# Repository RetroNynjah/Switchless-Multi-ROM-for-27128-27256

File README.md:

# Switchless Multi-ROM for 27128 & 27256 ROMs

<br/>

A switchless multi-ROM for 27128 and 27256 ROM (28-pin) type applications. The switch is controlled by an MCU that is picking up predefined magic words on the data bus.  
This is a more generic and further developed version of my previous 1541-II Multi-ROM design.

Example use cases:
* ROM switch for Commodore disk drives controlled by DOS commands.
* Menu driven Kernal switch for Commodore C64 (shortboards), Commodore C128 and Commodore TED series.
* You tell me

Check the Applications folder for examples on how to use it for the use cases above.

Check the Technical Guide for a general technical description, build instructions and BOM.

  <br/>

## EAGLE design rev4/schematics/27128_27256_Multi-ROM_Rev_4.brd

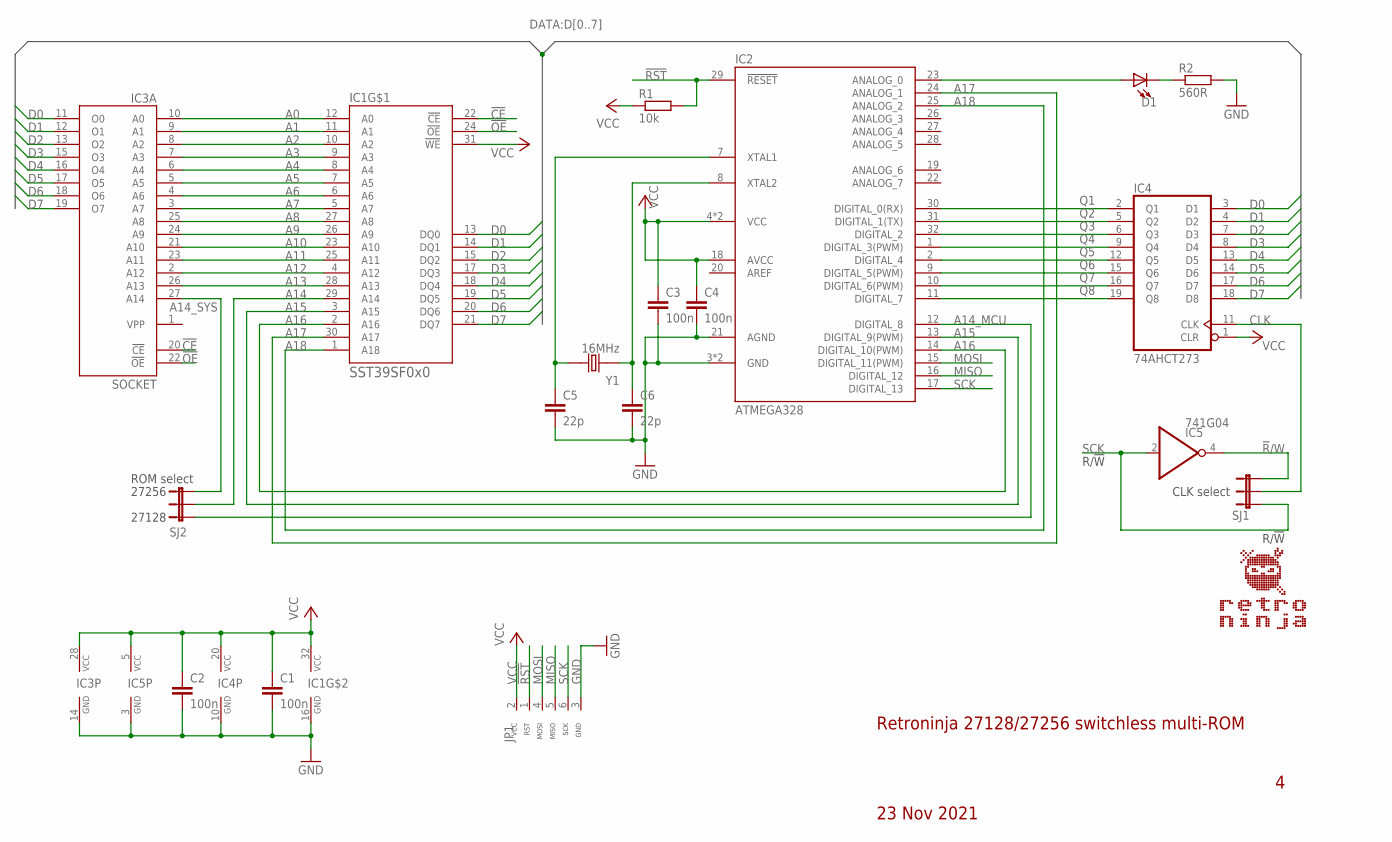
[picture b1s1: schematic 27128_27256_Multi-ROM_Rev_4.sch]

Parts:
C1, C2, C3, C4: 100n; C0805
C5, C6: 22p; C0805
D1: LED_0805; LED0805
IC1: SST39SF0x0; PLCC32_SHORT
IC2: ATMEGA328; TQFP32
IC3: SOCKET; DIL28-6_DOWNPINS
IC4: 74AHCT273; SO20
IC5: 741G04; SOT23-5
JP1: ICSP_CONNECTOR_TL866_RIGHT2; HEADER_1X6_RIGHT
R1: 10k; R0805
R2: 560R; R0805
SJ1, SJ2: JUMPER-3SJ; SJ-3
Y1: 16MHz; CRYSTAL_SMD-2_7X4X2.3

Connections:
!CE: IC1.22 (!CE), IC3.20 (!CE)
!OE: IC1.24 (!OE), IC3.22 (!OE)
!R!/W: IC5.4 (O), SJ1.3
!RST: IC2.29 (!RESET), JP1.1 (RST), R1.2
A0: IC1.12 (A0), IC3.10 (A0)
A1: IC1.11 (A1), IC3.9 (A1)
A2: IC1.10 (A2), IC3.8 (A2)
A3: IC1.9 (A3), IC3.7 (A3)
A4: IC1.8 (A4), IC3.6 (A4)
A5: IC1.7 (A5), IC3.5 (A5)
A6: IC1.6 (A6), IC3.4 (A6)
A7: IC1.5 (A7), IC3.3 (A7)
A8: IC1.27 (A8), IC3.25 (A8)
A9: IC1.26 (A9), IC3.24 (A9)
A10: IC1.23 (A10), IC3.21 (A10)
A11: IC1.25 (A11), IC3.23 (A11)
A12: IC1.4 (A12), IC3.2 (A12)
A13: IC1.28 (A13), IC3.26 (A13)
A14: IC1.29 (A14), SJ2.2
A14_MCU: IC2.12 (DIGITAL_8), SJ2.1
A14_SYS: IC3.27 (A14), SJ2.3
A15: IC1.3 (A15), IC2.13 (DIGITAL_9(PWM))
A16: IC1.2 (A16), IC2.14 (DIGITAL_10(PWM))
A17: IC1.30 (A17), IC2.24 (ANALOG_1)
A18: IC1.1 (A18), IC2.25 (ANALOG_2)
CLK: IC4.11 (CLK), SJ1.2
D0: IC1.13 (DQ0), IC3.11 (O0), IC4.3 (D1)
D1: IC1.14 (DQ1), IC3.12 (O1), IC4.4 (D2)
D2: IC1.15 (DQ2), IC3.13 (O2), IC4.7 (D3)
D3: IC1.17 (DQ3), IC3.15 (O3), IC4.8 (D4)
D4: IC1.18 (DQ4), IC3.16 (O4), IC4.13 (D5)
D5: IC1.19 (DQ5), IC3.17 (O5), IC4.14 (D6)
D6: IC1.20 (DQ6), IC3.18 (O6), IC4.17 (D7)
D7: IC1.21 (DQ7), IC3.19 (O7), IC4.18 (D8)
GND: C1.2, C2.2, C3.2, C4.2, C5.2, C6.2, IC1.16 (GND), IC2.3 (GND), IC2.5 (GND), IC2.21 (AGND), IC3.14 (GND), IC4.10 (GND), IC5.3 (GND), JP1.3 (GND), R2.2
MISO: IC2.16 (DIGITAL_12), JP1.5 (MISO)
MOSI: IC2.15 (DIGITAL_11(PWM)), JP1.4 (MOSI)
unnamed: C6.1, IC2.8 (XTAL2), Y1.1
unnamed: C5.1, IC2.7 (XTAL1), Y1.2
unnamed: D1.A, IC2.23 (ANALOG_0)
unnamed: D1.C, R2.1
Q1: IC2.30 (DIGITAL_0(RX)), IC4.2 (Q1)
Q2: IC2.31 (DIGITAL_1(TX)), IC4.5 (Q2)
Q3: IC2.32 (DIGITAL_2), IC4.6 (Q3)
Q4: IC2.1 (DIGITAL_3(PWM)), IC4.9 (Q4)
Q5: IC2.2 (DIGITAL_4), IC4.12 (Q5)
Q6: IC2.9 (DIGITAL_5(PWM)), IC4.15 (Q6)
Q7: IC2.10 (DIGITAL_6(PWM)), IC4.16 (Q7)
Q8: IC2.11 (DIGITAL_7), IC4.19 (Q8)
SCK: IC2.17 (DIGITAL_13), IC5.2 (I), JP1.6 (SCK), SJ1.1
VCC: C1.1, C2.1, C3.1, C4.1, IC1.31 (!WE), IC1.32 (VCC), IC2.4 (VCC), IC2.6 (VCC), IC2.18 (AVCC), IC3.28 (VCC), IC4.1 (CLR), IC4.20 (VCC), IC5.5 (VCC), JP1.2 (VCC), R1.1
VPP: IC3.1 (VPP)

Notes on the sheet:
Retroninja 27128/27256 switchless multi-ROM
23 Nov 2021
27128
27256
R/!W
CLK select
ROM select

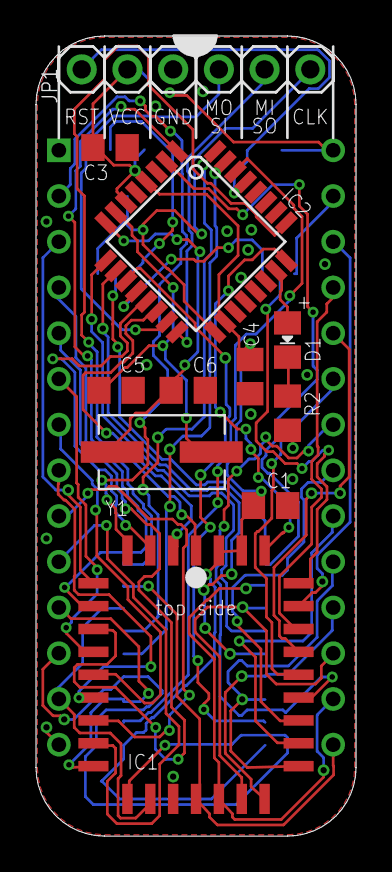
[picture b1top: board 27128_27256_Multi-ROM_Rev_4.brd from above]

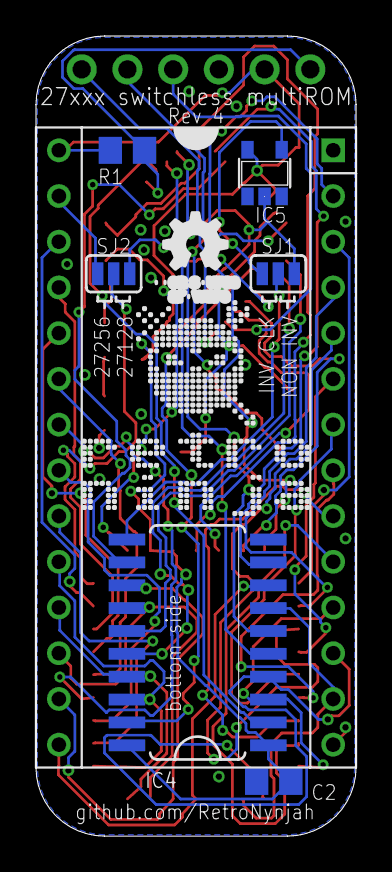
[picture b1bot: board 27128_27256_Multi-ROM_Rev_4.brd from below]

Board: 2 copper layers, 17.8 x 44.5 mm, 20 parts (8 on the bottom side), 51 nets.

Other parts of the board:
U$1: RETRONINJA_12MM
U$2: OSHW_5MM

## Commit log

2022-06-27 Initial upload
2022-08-20 Updated technical guide and multi-kernal user's guide
    Corrected errors in documentation
2022-09-06 Kernal switch C128DCR support
    New mini-kernals that send different commands for C128DCR switches. C64/C128 mini-kernal version numbers aligned.
    Added C128DCR firmware v 1.2. version number aligned with C128 firmware.
    Updated Kernal switch user guide to version 1.2 with added C128DCR solder point locations.
2022-09-06 Updated Kernal switch pictures and corrected user guide version
2022-09-07 Updated Kernal switch user guide
    User Guide version 1.4 with added information about Kernal ROM locations and sockets.
2022-11-30 Mini-kernals version 1.5 and C128 firmware 1.2.1
    Minor change in keyboard detection to try and mitigate key bounce in mini-kernal (C64+C128)
    Minor correction in C128 firmware
2022-12-01 Recompiled firmware for C64 shortboard kernal switch
    Recompiled firmware using DIY AVR core
2023-01-03 Firmware v1.4 for C64 and C128 Kernal switches
    Version numbers aligned between firmware for different Kernal switches as functionality is the pretty much same for all switches.
    Improved handling of restore key functionality while in menu to prevent switches from going into reset loop while holding restore.
    Code cleanup and some optimizations of main loop.
    Thanks Pär Högberg!
2023-01-10 New firmware version with support for 1571/1581.
    Reworked and heavily optimized firmware for drive ROM switch to support 1571 and 1581 if using 20MHz crystal.
    Updated documentation to reflect this change.
    Rebranded from Switchless multi-ROM for 1541-II to Switchless multi-ROM for CBM disk drives now that it supports quite a lot more drives.
    Thanks to Pär Högberg for contributing code optimizations.
2023-01-10 Create readme.md
    Folder moved to applications/Switchless multi-ROM for CBM disk drives
2023-04-17 Update README.md
    Comment about NTSC compatibility
2023-07-12 Updated C64 shortboard/C128 user guide
    Updated user guide to rev 1.5 with expanded information about R/W problems on some C128 boards.
2023-12-23 Plus/4 Kernal switch added to applications
    Updated technical guide and readme and added application directory for Plus/4 Kernal switch
2024-03-03 Added C16 documentation
2026-04-13 Clarify compatibility of Mini-Kernal with C16/C116
    Updated the README to clarify compatibility with C16 and C116.
